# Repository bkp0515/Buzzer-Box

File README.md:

# Buzzer-Box
A project designed to create an alternative solution to existing buzzer systems for bible quizzing.

## Features
The hardware revision 2 contains new features like a larger buzzer with hardware controllable volume courtousy of a PAM8904.
Additionally, the faceplate has been redesigned to operate on i2c communication to be removable with just a single 5 pin JST connection.
Being based on the ESP32 feather V2 by adafruit, bluetooth and wifi features will be added eventually. 
Build guide and BOM to come after prototyping hardware V2 is more solidified.

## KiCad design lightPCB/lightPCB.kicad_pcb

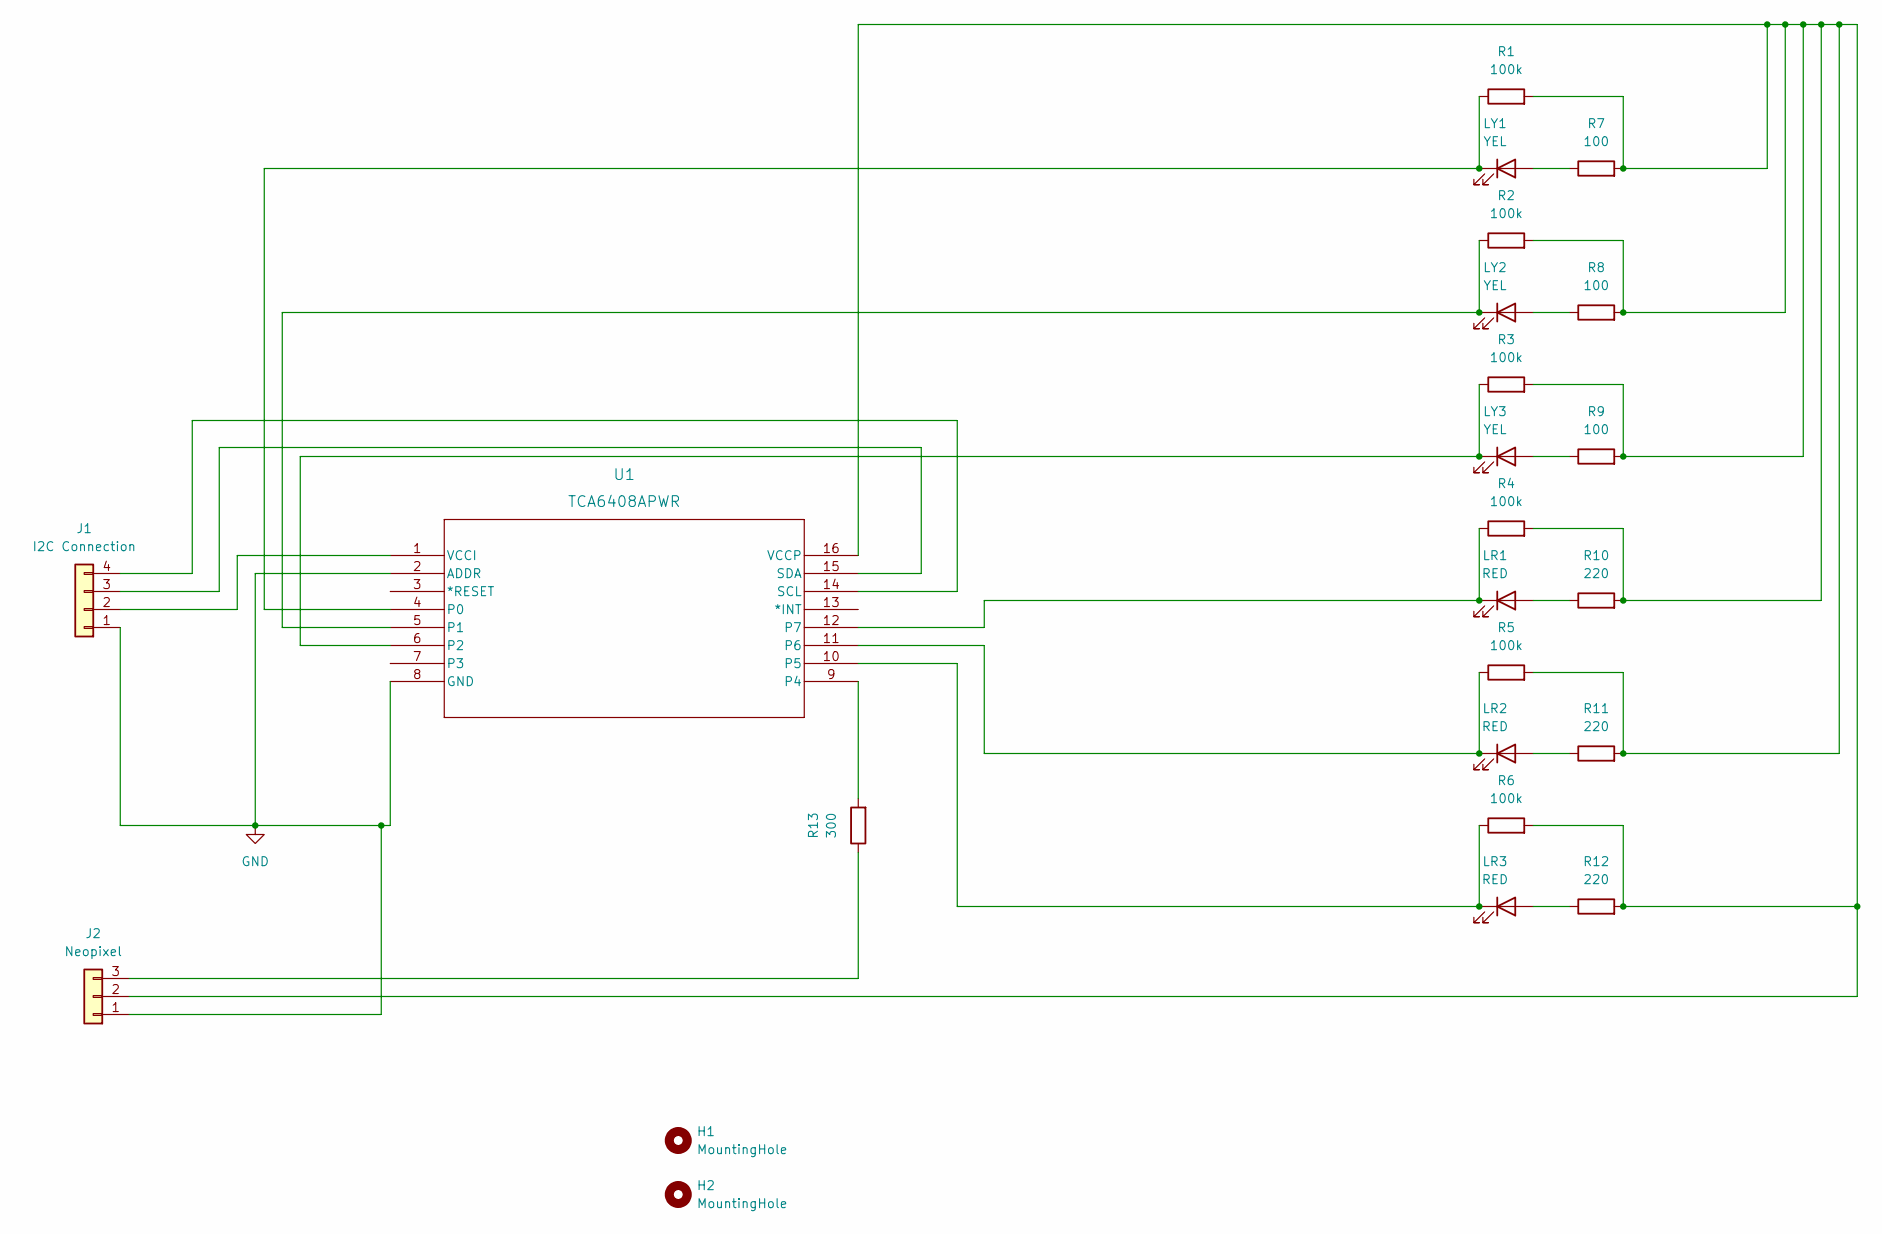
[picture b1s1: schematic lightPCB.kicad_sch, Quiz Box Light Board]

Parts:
H1, H2: MountingHole; MountingHole_2.2mm_M2_Pad
J1: I2C Connection; PinHeader_1x04_P2.54mm_Vertical
J2: Neopixel; PinHeader_1x03_P2.54mm_Vertical
LR1, LR2, LR3: RED; LED_D5.0mm
LY1, LY2, LY3: YEL; LED_D5.0mm
R1, R2, R3, R4, R5, R6: 100k; R_1206_3216Metric
R7, R8, R9: 100; R_1206_3216Metric
R10, R11, R12: 220; R_1206_3216Metric
R13: 300; R_1206_3216Metric
U1: TCA6408APWR; PW16

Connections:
GND: J1.1, J2.1, U1.2 (ADDR), U1.8 (GND)
unnamed: J1.2, U1.1 (VCCI)
unnamed: J2.3, R13.1
unnamed: LR1.2 (A), R10.1
unnamed: LR2.2 (A), R11.1
unnamed: LR3.2 (A), R12.1
unnamed: LY1.2 (A), R7.1
unnamed: LY2.2 (A), R8.1
unnamed: LY3.2 (A), R9.1
unnamed: LY1.1 (K), R1.1, U1.4 (P0)
unnamed: LY2.1 (K), R2.1, U1.5 (P1)
unnamed: LY3.1 (K), R3.1, U1.6 (P2)
unnamed: R13.2, U1.9 (P4)
unnamed: LR3.1 (K), R6.1, U1.10 (P5)
unnamed: LR2.1 (K), R5.1, U1.11 (P6)
unnamed: LR1.1 (K), R4.1, U1.12 (P7)
unnamed: J1.4, U1.14 (SCL)
unnamed: J1.3, U1.15 (SDA)
unnamed: J2.2, R1.2, R2.2, R3.2, R4.2, R5.2, R6.2, R7.2, R8.2, R9.2, R10.2, R11.2, R12.2, U1.16 (VCCP)

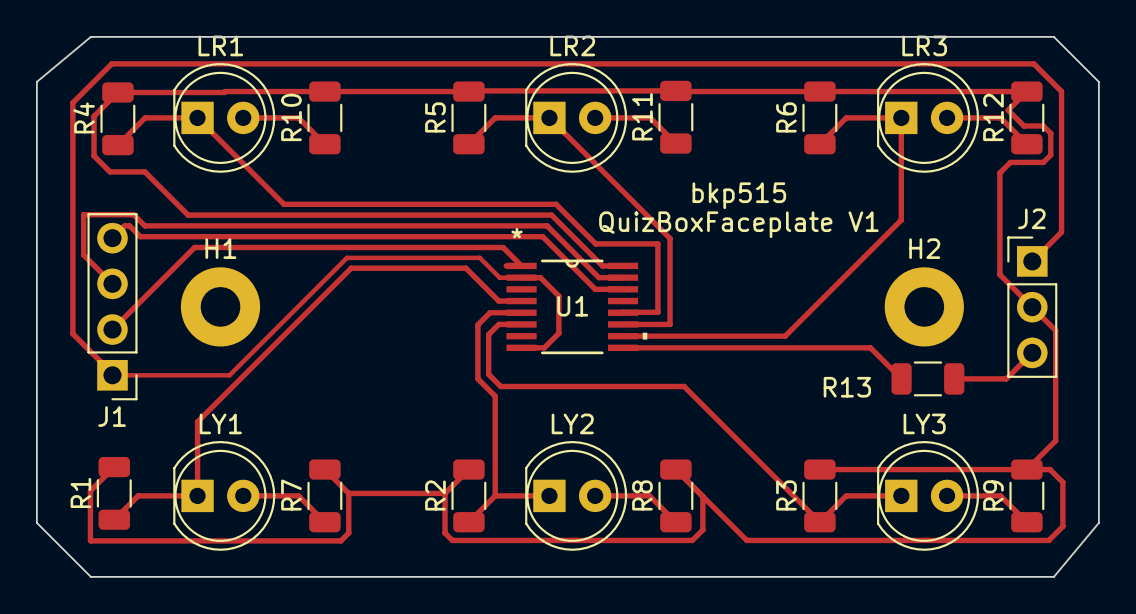
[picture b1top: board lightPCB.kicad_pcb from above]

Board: 2 copper layers, 59.0 x 30.0 mm, 24 parts (0 on the bottom side), 19 nets.

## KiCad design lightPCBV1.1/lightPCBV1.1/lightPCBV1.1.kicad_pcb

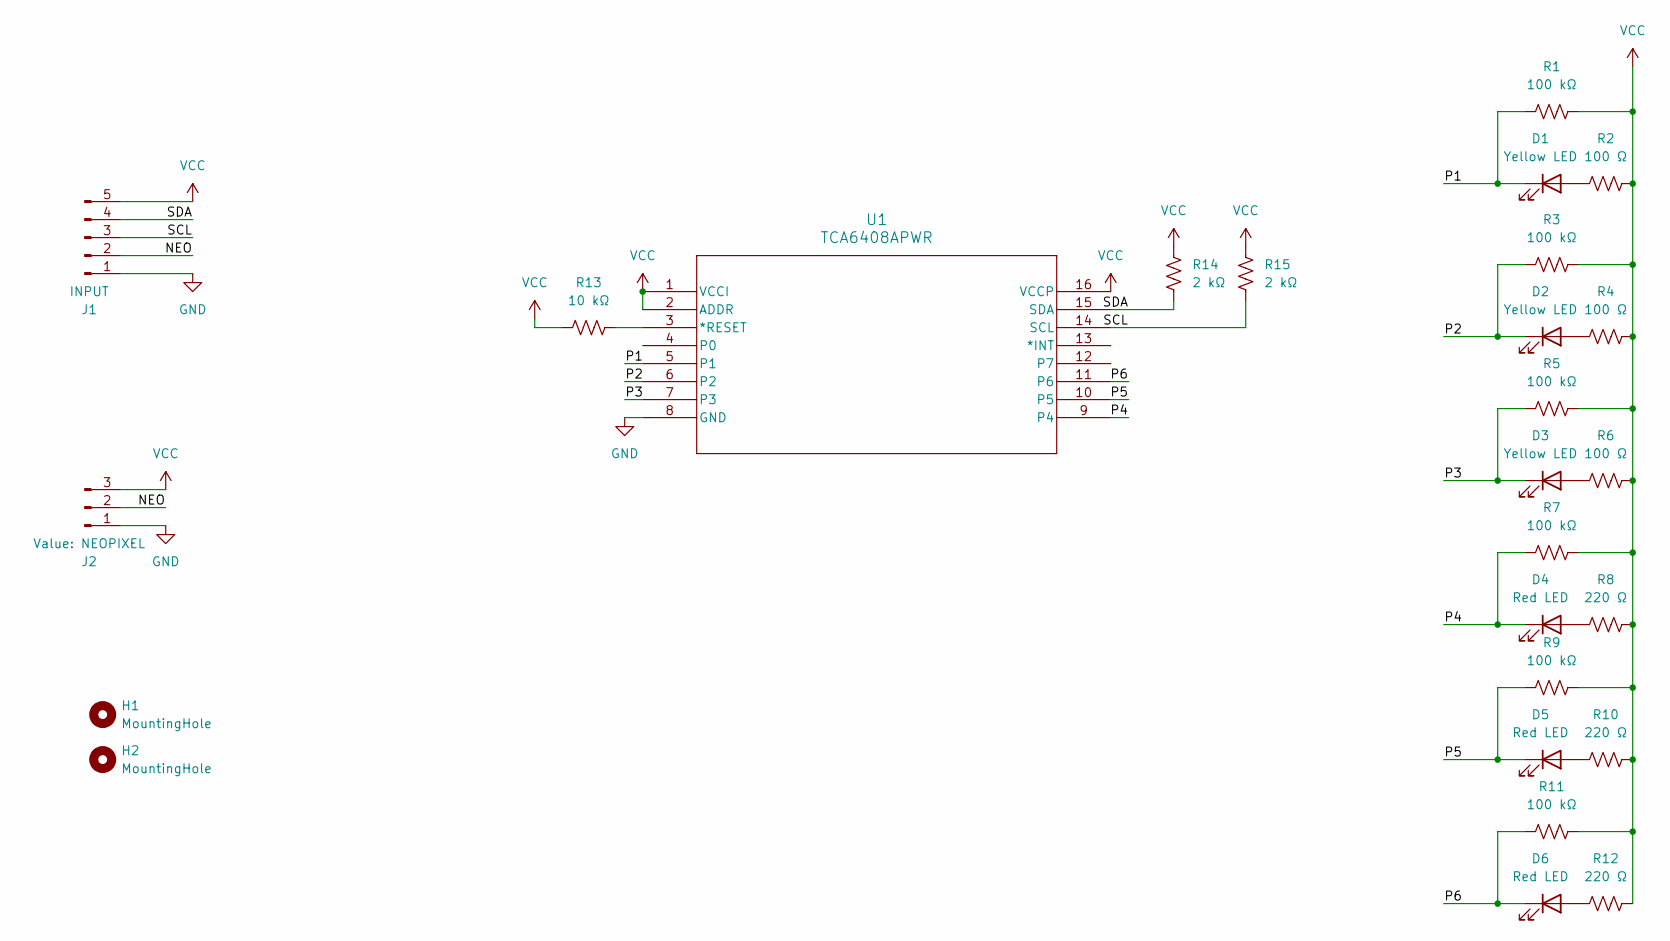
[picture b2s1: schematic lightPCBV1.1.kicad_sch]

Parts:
D1, D2, D3: Yellow LED; LED_D5.0mm
D4, D5, D6: Red LED; LED_D5.0mm
H1, H2: MountingHole; MountingHole_2.2mm_M2
J1: INPUT; JST_PH_B5B-PH-K_1x05_P2.00mm_Vertical
J2: NEOPIXEL; PinHeader_1x03_P2.54mm_Vertical
R1, R3, R5, R7, R9, R11: 100 kΩ; R_1206_3216Metric_Pad1.30x1.75mm_HandSolder
R2, R4, R6: 100 Ω; R_1206_3216Metric_Pad1.30x1.75mm_HandSolder
R8, R10, R12: 220 Ω; R_1206_3216Metric_Pad1.30x1.75mm_HandSolder
R13: 10 kΩ; R_1206_3216Metric_Pad1.30x1.75mm_HandSolder
R14, R15: 2 kΩ; R_1206_3216Metric_Pad1.30x1.75mm_HandSolder
U1: TCA6408APWR; PW16

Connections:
/NEO: J1.2, J2.2
/P1: D1.1 (K), R1.1, U1.5 (P1)
/P2: D2.1 (K), R3.1, U1.6 (P2)
/P3: D3.1 (K), R5.1, U1.7 (P3)
/P4: D4.1 (K), R7.1, U1.9 (P4)
/P5: D5.1 (K), R9.1, U1.10 (P5)
/P6: D6.1 (K), R11.1, U1.11 (P6)
/SCL: J1.3, R15.2, U1.14 (SCL)
/SDA: J1.4, R14.1, U1.15 (SDA)
GND: J1.1, J2.1, U1.8 (GND)
unnamed: D1.2 (A), R2.1
unnamed: D2.2 (A), R4.1
unnamed: D3.2 (A), R6.1
unnamed: D4.2 (A), R8.1
unnamed: D5.2 (A), R10.1
unnamed: D6.2 (A), R12.1
unnamed: R13.2, U1.3 (*RESET)
VCC: J1.5, J2.3, R1.2, R2.2, R3.2, R4.2, R5.2, R6.2, R7.2, R8.2, R9.2, R10.2, R11.2, R12.2, R13.1, R14.2, R15.1, U1.1 (VCCI), U1.2 (ADDR), U1.16 (VCCP)

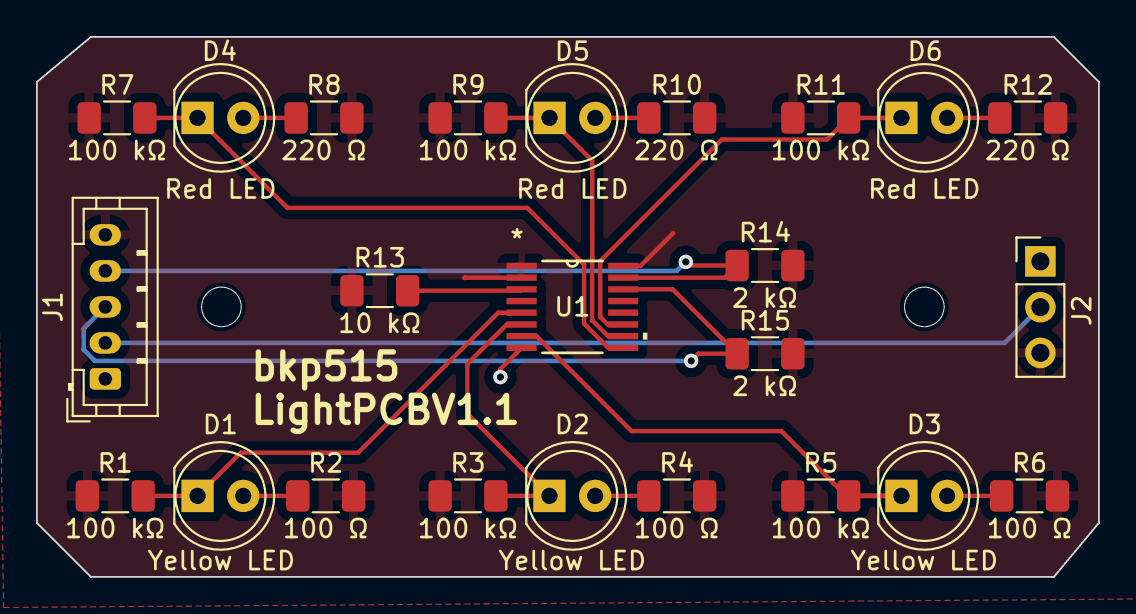
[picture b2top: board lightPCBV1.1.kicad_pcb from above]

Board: 2 copper layers, 59.0 x 30.0 mm, 26 parts (0 on the bottom side), 18 nets.

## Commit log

2023-02-22 Another initial commit
2023-02-22 Created interrupts for new interrupt system of buzzing Created a function for red 1 to buzz adjusted timer function to fix non reloading
2023-02-22 fixed timer not restarting after first buzz
2023-02-22 Added buzzer timer and actual buzzing to red 1 buzz in function
2023-02-22 Duplicated the buzz functino for the other buzzers, started causing problems exiting the buzz function
2023-03-12 Replaced adafruit neopixel library with the fast led library to improve interrupt performace. Still having buzzes after timer runs out.
2023-08-04 Started work on a new PCB for the jacks to reduce hand wiring
2023-10-14 Designed a new faceplace pcb and created a new test program to interface with the tca ic
